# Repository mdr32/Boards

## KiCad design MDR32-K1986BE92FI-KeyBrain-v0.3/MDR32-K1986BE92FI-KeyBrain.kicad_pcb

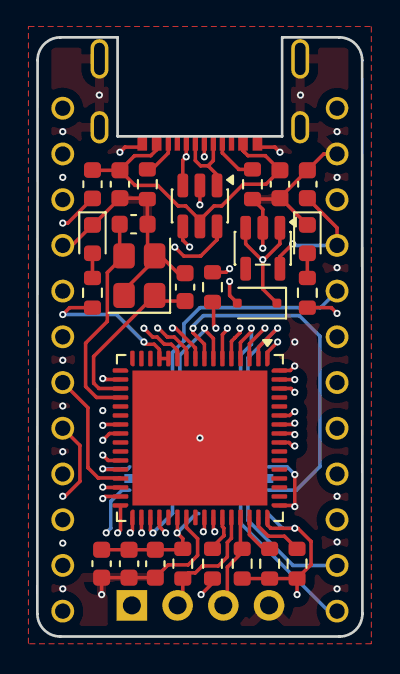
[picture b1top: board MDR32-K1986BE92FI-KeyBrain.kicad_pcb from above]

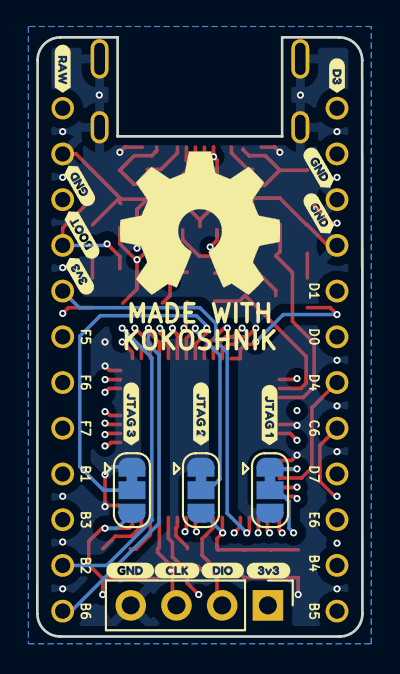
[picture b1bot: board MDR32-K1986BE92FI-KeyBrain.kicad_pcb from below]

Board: 4 copper layers, 18.1 x 33.3 mm, 46 parts (18 on the bottom side), 44 nets.

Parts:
C1: 1μF; C_0603_1608Metric
C2, C5: 10pF; C_0603_1608Metric
C3: 10μF; C_0603_1608Metric
C4, C6, C7, C8: 0.1μF; C_0603_1608Metric
D1: 3A/10V/280mV; D_SOD-323F
D2: RED; LED_0603_1608Metric
D3: GREEN; LED_0603_1608Metric
F1: 6V 0.5A MF-FSMF050X-2; Fuse_0603_1608Metric
J1: USB-C USB 2.0 MC-372; USB-C_C168688
J2: SWD; PinHeader_1x04_P2.54mm_Vertical
JP1: MODE0; SolderJumper-3_P1.3mm_Bridged12_RoundedPad1.0x1.5mm
JP2: MODE1; SolderJumper-3_P1.3mm_Bridged12_RoundedPad1.0x1.5mm
JP3: MODE2; SolderJumper-3_P1.3mm_Bridged12_RoundedPad1.0x1.5mm
R1, R2, R3, R4, R5, R6: 10K; R_0603_1608Metric
R7, R8: 5.1K; R_0603_1608Metric
R9, R10: 1K; R_0603_1608Metric
U1: AP2112K-3.3; SOT-23-5
U2: USBLC6-2SC6; SOT-23-6
U3: K1986BE92FI; QFN-64-1EP_9x9mm_P0.5mm_EP7.5x7.5mm
U4: ProMicro; pro_micro
Y1: 8MHz; Crystal_SMD_3225-4Pin_3.2x2.5mm
kibuzzard-6AC7C5DE: G***; kibuzzard-6AC7C5DE
kibuzzard-6AC7C68D, kibuzzard-6AC7C68D#2, kibuzzard-6AC7C68D#3: G***; kibuzzard-6AC7C68D
kibuzzard-6AC7C647: G***; kibuzzard-6AC7C647
kibuzzard-6ACB3A3D: G***; kibuzzard-6ACB3A3D
kibuzzard-6ACB3A18: G***; kibuzzard-6ACB3A18
kibuzzard-6ACB38A4: G***; kibuzzard-6ACB38A4
kibuzzard-6ACB38AF: G***; kibuzzard-6ACB38AF
kibuzzard-6ACB39CC: G***; kibuzzard-6ACB39CC
kibuzzard-6ACB39EC: G***; kibuzzard-6ACB39EC
kibuzzard-6ACB396A: G***; kibuzzard-6ACB396A
kibuzzard-6ACB398C: G***; kibuzzard-6ACB398C
kibuzzard-6ACB3944: G***; kibuzzard-6ACB3944

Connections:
+3.3V: C3.1, C6.1, C7.1, C8.1, J2.1, JP1.1 (A), JP2.3 (B), JP3.3 (B), R1.2, R2.2, R3.2, R4.2, R5.2, R6.2, R9.2, U1.5 (VOUT), U3.1 (UCC), U3.12 (UCC), U3.13 (BUCC), U3.24 (AUCC1), U3.28 (AUCC), U3.38 (UCC), U3.48 (UCC), U4.4 (VCC)
+5V: D1.1 (K), U1.1 (VIN), U1.3 (EN), U4.1 (RAW)
/0/TX0: U3.56 (PA7), U4.13 (PD3)
/1/RX0: U3.57 (PA6), U4.14 (PD2)
/2/SDA: U3.41 (PC1), U4.17 (PD1)
/3/SCL: U3.42 (PC0), U4.18 (PD0)
/4: U3.29 (PD7), U4.19 (PD4)
/5: U3.58 (PA5), U4.20 (PC6)
/6: U3.36 (PD6), U4.21 (PD7)
/7: U3.63 (PA0), U4.22 (PE6)
/8/TX1: U3.32 (PD1), U4.23 (PB4)
/9/RX1: U3.31 (PD0), U4.24 (PB5)
/20/SPI_CIPO: U3.5 (PF3), U4.10 (PB3)
/21/SPI_~CS: U3.4 (PF2), U4.12 (PB6)
/22/SPI_SCK: U3.3 (PF1), U4.9 (PB1)
/23/SPI_COPI: U3.2 (PF0), U4.11 (PB2)
/A0: U3.33 (PD2), U4.8 (PF7)
/A1: U3.34 (PD3), U4.7 (PF6)
/A2: U3.30 (PD4), U4.6 (PF5)
/A3: U3.35 (PD5), U4.5 (PF4)
/CLK: J2.3, R2.1, U3.45 (PB2)
/D+: J1.A6 (D+), J1.B6 (D+), U2.3 (I/O2)
/D-: J1.A7 (D-), J1.B7 (D-), U2.1 (I/O1)
/DATA+: U2.4 (I/O2), U3.9 (DP)
/DATA-: U2.6 (I/O1), U3.10 (DN)
/DIO: J2.2, R1.1, U3.44 (PB1)
/JATDI: R4.1, U3.46 (PB3)
/JATDO: R5.1, U3.43 (PB0)
/JAnTRS: R3.1, U3.47 (PB4)
/JTAG_MODE1: JP1.2 (C), U3.6 (PF4)
/JTAG_MODE2: JP2.2 (C), U3.7 (PF5)
/JTAG_MODE3: JP3.2 (C), U3.8 (PF6)
/OSC_IN: C2.1, U3.19 (OSC_IN), Y1.1
/OSC_OUT: C5.1, U3.20 (OSC_OUT), Y1.3
/USRBTN: U3.62 (PA1), U4.3 (RST)
/USRLED: R10.2, U3.59 (PA4)
/nRESET: R6.1, U3.18 (~RESET)
GND: C1.2, C2.2, C3.2, C4.2, C5.2, C6.2, C7.2, C8.2, D2.1 (K), D3.1 (K), J1.A1 (GND), J1.S1, J2.4, JP1.3 (B), JP2.1 (A), JP3.1 (A), R7.2, R8.2, U1.2 (GND), U2.2 (GND), U3.11 (GND), U3.23 (AGND1), U3.27 (AGND), U3.39 (GND), U3.49 (GND), U3.64 (GND), U3.65 (PAD), U4.2 (GND), U4.15 (GND), U4.16 (GND), Y1.2 (G), Y1.4 (G)
unnamed: D1.2 (A), F1.2
unnamed: D2.2 (A), R9.1
unnamed: D3.2 (A), R10.1
unnamed: J1.A5 (CC1), R8.1
unnamed: J1.B5 (CC2), R7.1
VBUS: C1.1, C4.1, F1.1, J1.A4 (VBUS), U2.5 (VBUS)

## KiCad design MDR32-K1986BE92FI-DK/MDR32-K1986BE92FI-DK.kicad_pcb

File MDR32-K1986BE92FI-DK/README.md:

# MDR32-K1986BE92FI-DK (Doublemint) - Отладочная плата

Отладочная плата на микроконтроллере [K1986BE92FI](https://ic.milandr.ru/products/mikrokontrollery_i_protsessory/32_razryadnye_mikrokontrollery/k1986ve92fi) от компании [Milandr](https://milandr.ru/)

## Пользовательские элементы управления:

* `RST` - кнопка для сброса питания, осуществляет полное обесточивание всей цепи питания микроконтроллера, в т.ч. даже если питание платы осуществлено через `SWD`-коннектор программатора;
* `LED GREEN` - светодиод, сигнализирующий о наличии питания платы, *не имеет обозначения на плате*;
* `USR` - пользовательская кнопка, подключена к пину `PD5`;
* `LED BLUE` - пользовательский светодиод, подключен к пину `PC2`, *не имеет обозначения на плате*;

## Особенности

Плата выполнена только для внутренних целей, тестирования возможностей микроконтроллера и разработки модулей, т.е. широкопрофильна.

По вышеуказанным целя, плата имеет свои **особенности**:

* смотри на конденсаторы на второй стороне платы, размещаются максимально близко к пинам;

* присутствуют самовосстанавливаюшщиеся предохранители на линиях `D+` и `D-` данных `USB`;

* питание платы осуществляется от USB Type-C `5V DC` или от SWD-пинов `3.3V DC`;

* на плате предусмотрен линейный понижающий регулятор до `1А`, на случай если необходимо осуществить питание переферии от самой платы;

* перемычки пинов `PE6` и `PE7`, при замыкании которых будут использоваться именно эти пины вместо часового кварцевого резонатора на `32.768KHz` (соответственно, сам резонатор и его конденсаторы должны отсутствовать на плате);

* присутствует возможность пдключения батареи (при работе батареи необходимо перевести переключатель `BT > ON`. **Важно!** Переключение выполнить согласно шелкографии, а не обозначения на групповом переключателе);

* на штыревую гребенку выведены опциональные пины `MODE[0..1]` (пины `PF4-6`) режимов работы микроконтроллера, чтобы можно было ими манипулировать для целей разработки;

Также, плата имеет свои ограничения:
* разводка платы не расчитана на высокоскоростную работу с USB;
* нет разделения по аналоговому и общему питанию, поэтому работа с аналоговым сигналом не гарантирует правильную работу$
* `USB Type-C` используется только как `USB2.0`, настоен только на `5V DC`.

---

## Демо платы:

Видеообзор платы от известного в узких кругах российского видеоблогера, смотрите на [YouTube](https://www.youtube.com/watch?v=NqpC7BkRngA) или [Rutube](https://rutube.ru/video/9d385670fd4b314179d501ec34238957/?r=wd).

> [Смотреть схему в PDF-формате](./sch_MDR32-K1986BE92FI-DK.pdf)

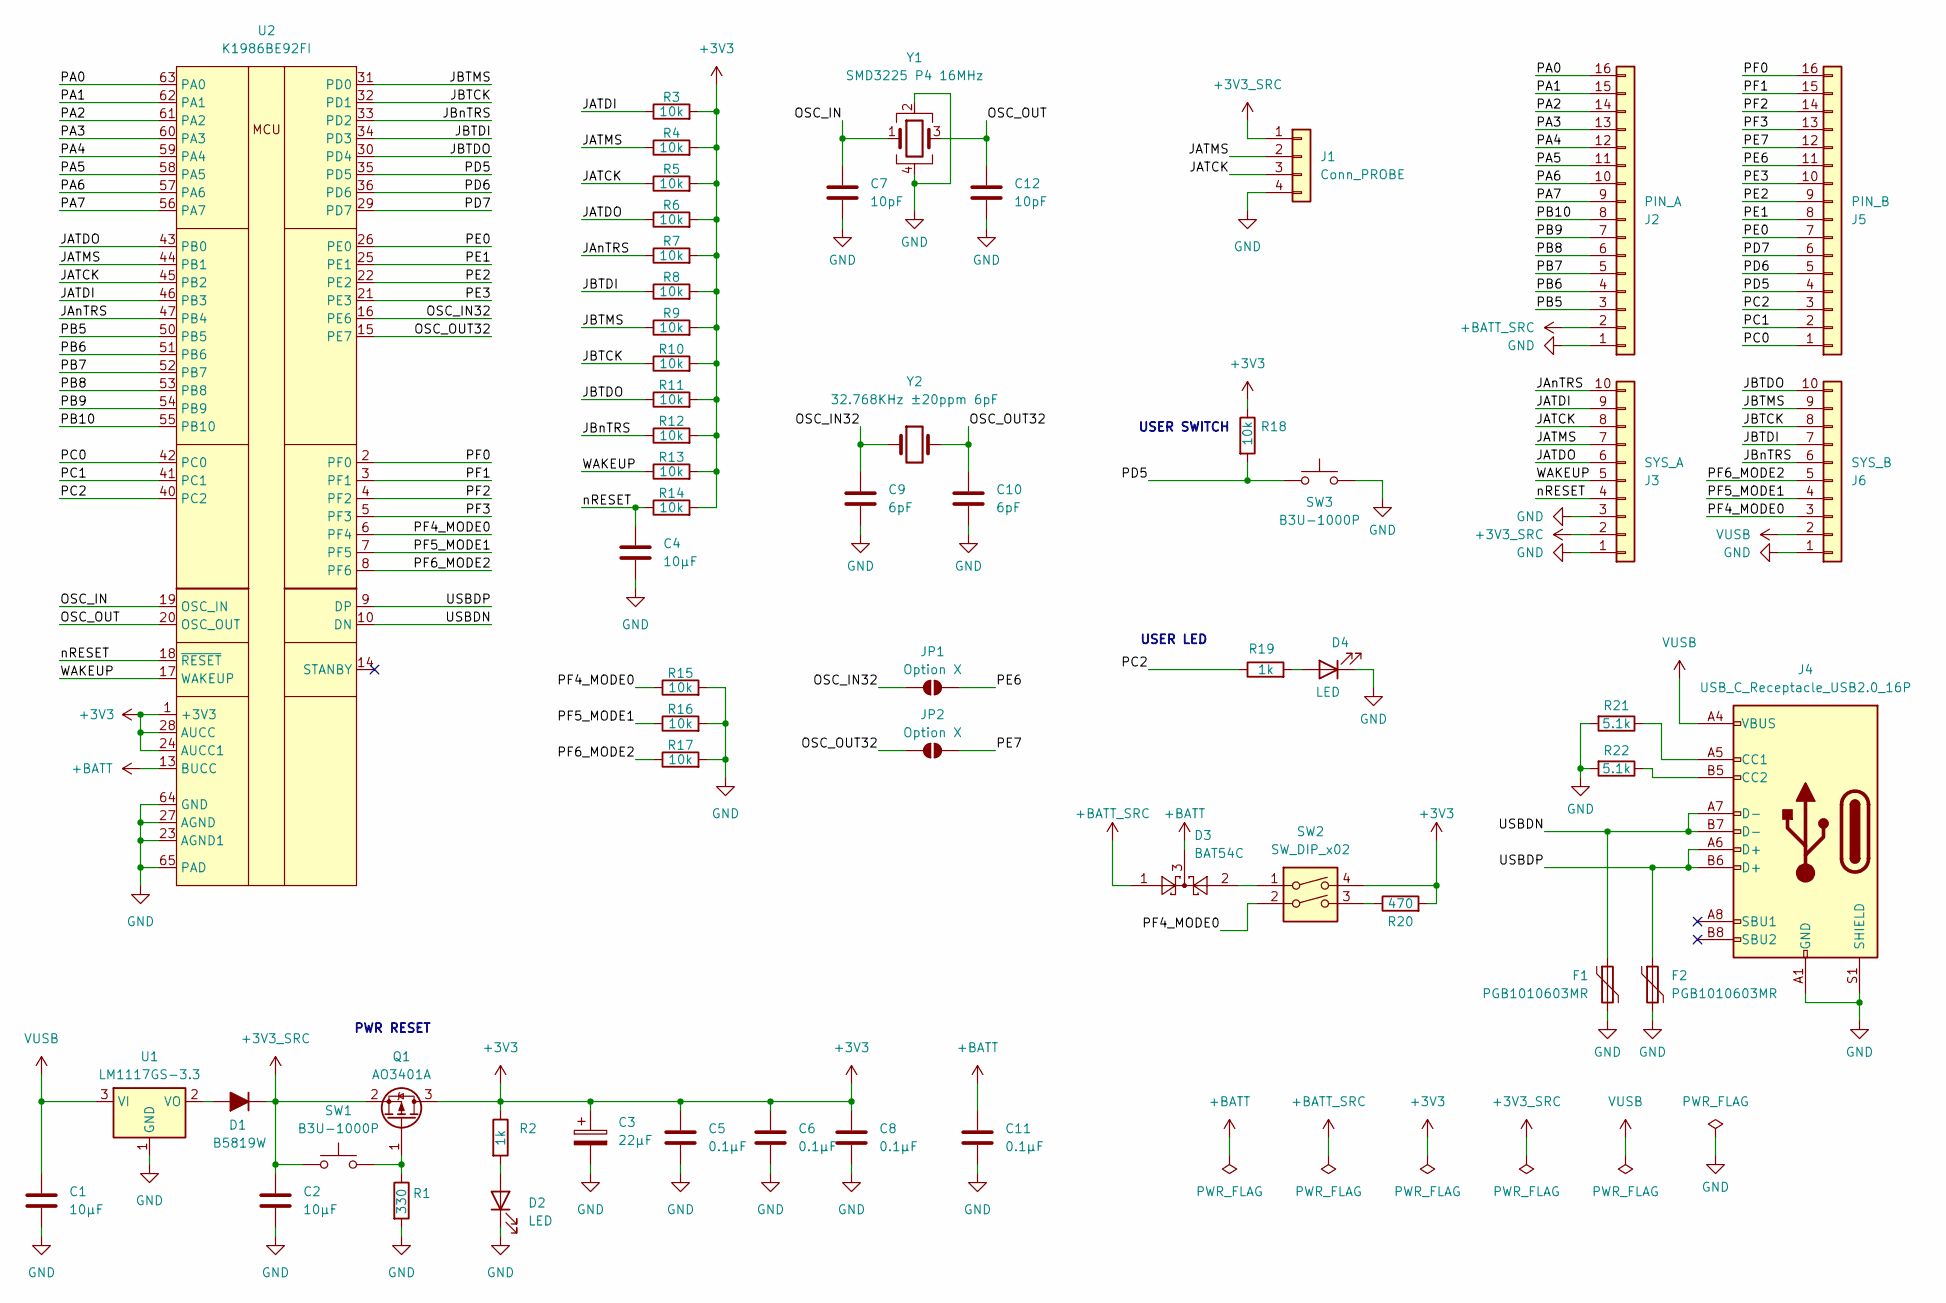
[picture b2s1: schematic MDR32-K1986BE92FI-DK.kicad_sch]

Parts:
C1, C2: 10µF; C_0805_2012Metric
C3: 22µF; CP_EIA-3216-18_Kemet-A
C4: 10µF; C_0603_1608Metric
C5, C6, C8, C11: 0.1µF; C_0603_1608Metric
C7, C12: 10pF; C_0603_1608Metric
C9, C10: 6pF; C_0603_1608Metric
D1: B5819W; D_SOD-123
D2, D4: LED; LED_0805_2012Metric
D3: BAT54C; SOT-23
F1, F2: PGB1010603MR; Fuse_0603_1608Metric
J1: Conn_PROBE; PinHeader_1x04_P2.54mm_Horizontal
J2: PIN_A; PinHeader_1x16_P2.54mm_Vertical
J3: SYS_A; PinHeader_1x10_P2.54mm_Vertical
J4: USB_C_Receptacle_USB2.0_16P; USB_C_Receptacle_GCT_USB4105-xx-A_16P_TopMnt_Horizontal
J5: PIN_B; PinHeader_1x16_P2.54mm_Vertical
J6: SYS_B; PinHeader_1x10_P2.54mm_Vertical
JP1, JP2: Option X; SolderJumper-2_P1.3mm_Open_TrianglePad1.0x1.5mm
Q1: AO3401A; SOT-23
R1: 330; R_0603_1608Metric
R2, R19: 1k; R_0603_1608Metric
R3, R4, R5, R6, R7, R8, R9, R10, R11, R12, R13, R14, R15, R16, R17, R18: 10k; R_0603_1608Metric
R20: 470; R_0603_1608Metric
R21, R22: 5.1k; R_0603_1608Metric
SW1, SW3: B3U-1000P; SW_SPST_B3U-1000P
SW2: SW_DIP_x02; SW_DIP_SPSTx02_Slide_Omron_A6H-2101_W6.15mm_P1.27mm
U1: LM1117GS-3.3; SOT-223
U2: K1986BE92FI; QFN-64-1EP_9x9mm_P0.5mm_EP7.5x7.5mm
Y1: SMD3225 P4 16MHz; Crystal_SMD_3225-4Pin_3.2x2.5mm
Y2: 32.768KHz ±20ppm 6pF; Crystal_SMD_3215-2Pin_3.2x1.5mm

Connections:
+3V3: C3.1, C5.1, C6.1, C8.1, Q1.3 (D), R2.1, R3.2, R4.2, R5.2, R6.2, R7.2, R8.2, R9.2, R10.2, R11.2, R12.2, R13.2, R14.2, R18.1, R20.2, SW2.4, U2.1 (+3V3), U2.24 (AUCC1), U2.28 (AUCC)
+3V3_SRC: C2.1, D1.1 (K), J1.1, J3.2, Q1.2 (S), SW1.1
+BATT: C11.1, D3.3, U2.13 (BUCC)
+BATT_SRC: D3.1, J2.2
/JATCK: J1.3, J3.8, R5.1, U2.45 (PB2)
/JATDI: J3.9, R3.1, U2.46 (PB3)
/JATDO: J3.6, R6.1, U2.43 (PB0)
/JATMS: J1.2, J3.7, R4.1, U2.44 (PB1)
/JAnTRS: J3.10, R7.1, U2.47 (PB4)
/JBTCK: J6.8, R10.1, U2.32 (PD1)
/JBTDI: J6.7, R8.1, U2.34 (PD3)
/JBTDO: J6.10, R11.1, U2.30 (PD4)
/JBTMS: J6.9, R9.1, U2.31 (PD0)
/JBnTRS: J6.6, R12.1, U2.33 (PD2)
/OSC_IN: C7.1, U2.19 (OSC_IN), Y1.1
/OSC_IN32: C9.1, JP1.1 (A), U2.16 (PE6), Y2.1
/OSC_OUT: C12.1, U2.20 (OSC_OUT), Y1.3
/OSC_OUT32: C10.1, JP2.1 (A), U2.15 (PE7), Y2.2
/PA0: J2.16, U2.63 (PA0)
/PA1: J2.15, U2.62 (PA1)
/PA2: J2.14, U2.61 (PA2)
/PA3: J2.13, U2.60 (PA3)
/PA4: J2.12, U2.59 (PA4)
/PA5: J2.11, U2.58 (PA5)
/PA6: J2.10, U2.57 (PA6)
/PA7: J2.9, U2.56 (PA7)
/PB5: J2.3, U2.50 (PB5)
/PB6: J2.4, U2.51 (PB6)
/PB7: J2.5, U2.52 (PB7)
/PB8: J2.6, U2.53 (PB8)
/PB9: J2.7, U2.54 (PB9)
/PB10: J2.8, U2.55 (PB10)
/PC0: J5.1, U2.42 (PC0)
/PC1: J5.2, U2.41 (PC1)
/PC2: J5.3, R19.1, U2.40 (PC2)
/PD5: J5.4, R18.2, SW3.1, U2.35 (PD5)
/PD6: J5.5, U2.36 (PD6)
/PD7: J5.6, U2.29 (PD7)
/PE0: J5.7, U2.26 (PE0)
/PE1: J5.8, U2.25 (PE1)
/PE2: J5.9, U2.22 (PE2)
/PE3: J5.10, U2.21 (PE3)
/PE6: J5.11, JP1.2 (B)
/PE7: J5.12, JP2.2 (B)
/PF0: J5.16, U2.2 (PF0)
/PF1: J5.15, U2.3 (PF1)
/PF2: J5.14, U2.4 (PF2)
/PF3: J5.13, U2.5 (PF3)
/PF4_MODE0: J6.3, R15.1, SW2.2, U2.6 (PF4)
/PF5_MODE1: J6.4, R16.1, U2.7 (PF5)
/PF6_MODE2: J6.5, R17.1, U2.8 (PF6)
/USBDN: F1.1, J4.A7 (D-), J4.B7 (D-), U2.10 (DN)
/USBDP: F2.1, J4.A6 (D+), J4.B6 (D+), U2.9 (DP)
/WAKEUP: J3.5, R13.1, U2.17 (WAKEUP)
/nRESET: C4.1, J3.4, R14.1, U2.18 (~RESET)
GND: C1.2, C2.2, C3.2, C4.2, C5.2, C6.2, C7.2, C8.2, C9.2, C10.2, C11.2, C12.2, D2.1 (K), D4.1 (K), F1.2, F2.2, J1.4, J2.1, J3.1, J3.3, J4.A1 (GND), J4.A12 (GND), J4.B1 (GND), J4.B12 (GND), J4.S1 (SHIELD), J6.1, R1.2, R15.2, R16.2, R17.2, R21.2, R22.2, SW3.2, U1.1 (GND), U2.11 (GND), U2.23 (AGND1), U2.27 (AGND), U2.39 (GND), U2.49 (GND), U2.64 (GND), U2.65 (PAD), Y1.2, Y1.4
unnamed: D1.2 (A), U1.2 (VO)
unnamed: D2.2 (A), R2.2
unnamed: D3.2, SW2.1
unnamed: D4.2 (A), R19.2
unnamed: J4.A5 (CC1), R21.1
unnamed: J4.B5 (CC2), R22.1
unnamed: Q1.1 (G), R1.1, SW1.2
unnamed: R20.1, SW2.3
VUSB: C1.1, J4.A4 (VBUS), J4.A9 (VBUS), J4.B4 (VBUS), J4.B9 (VBUS), J6.2, U1.3 (VI)

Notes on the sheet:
USER LED
PWR RESET
USER SWITCH

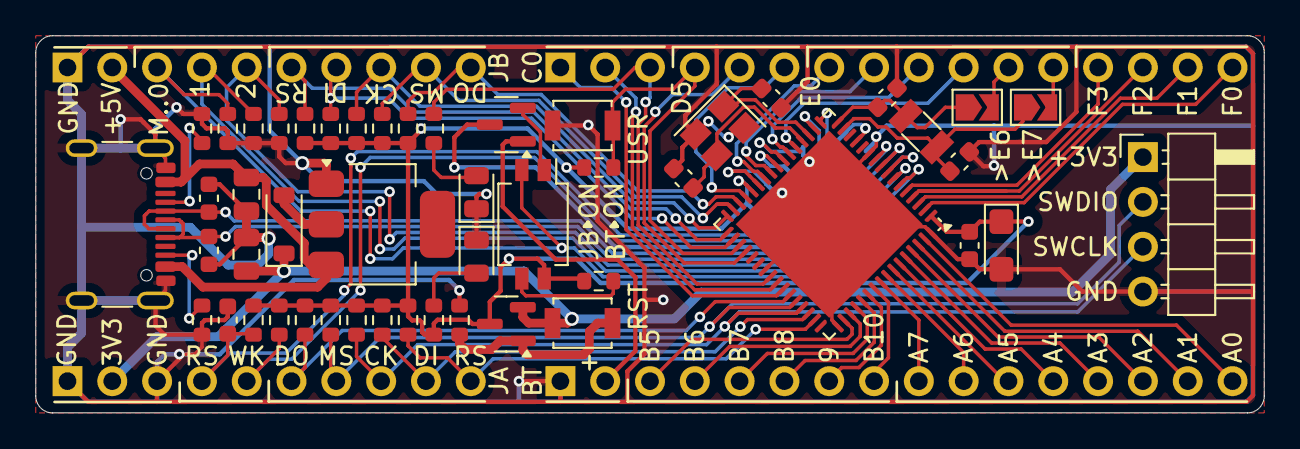
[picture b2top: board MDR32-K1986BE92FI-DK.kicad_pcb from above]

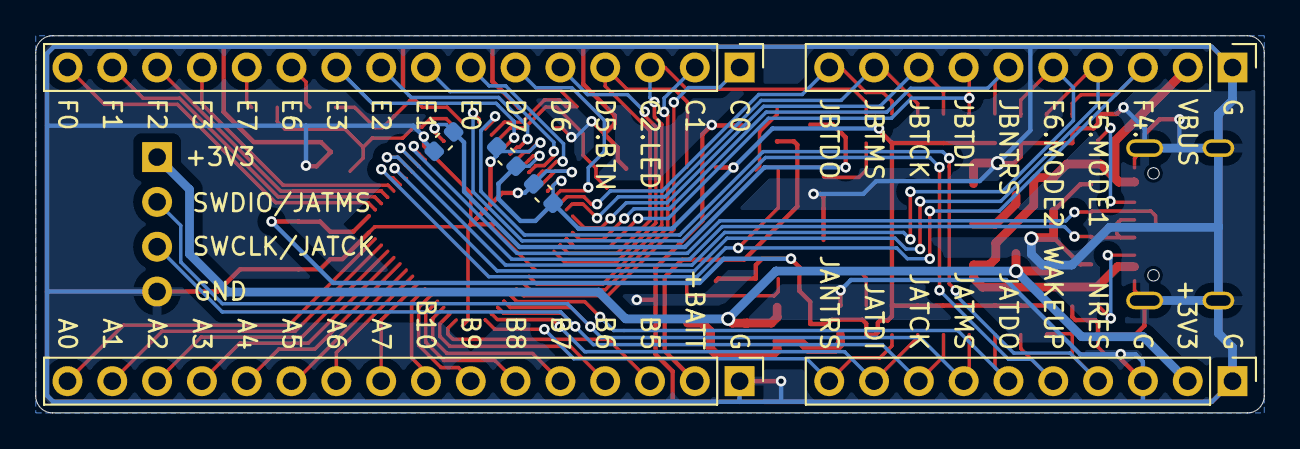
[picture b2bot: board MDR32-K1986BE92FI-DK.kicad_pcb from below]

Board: 2 copper layers, 69.6 x 21.4 mm, 56 parts (7 on the bottom side), 65 nets.

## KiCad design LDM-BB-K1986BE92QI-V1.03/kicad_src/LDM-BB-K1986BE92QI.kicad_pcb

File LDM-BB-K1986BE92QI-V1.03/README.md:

# [LDM-BB-K1986BE92QI](https://ldm-systems.ru/product/19025) - Отладочная плата

Отладочная плата на микроконтроллере [K1986BE92QI](https://ic.milandr.ru/products/mikrokontrollery_i_protsessory/32_razryadnye_mikrokontrollery/k1986ve92qi) от компании [Milandr](https://milandr.ru/)

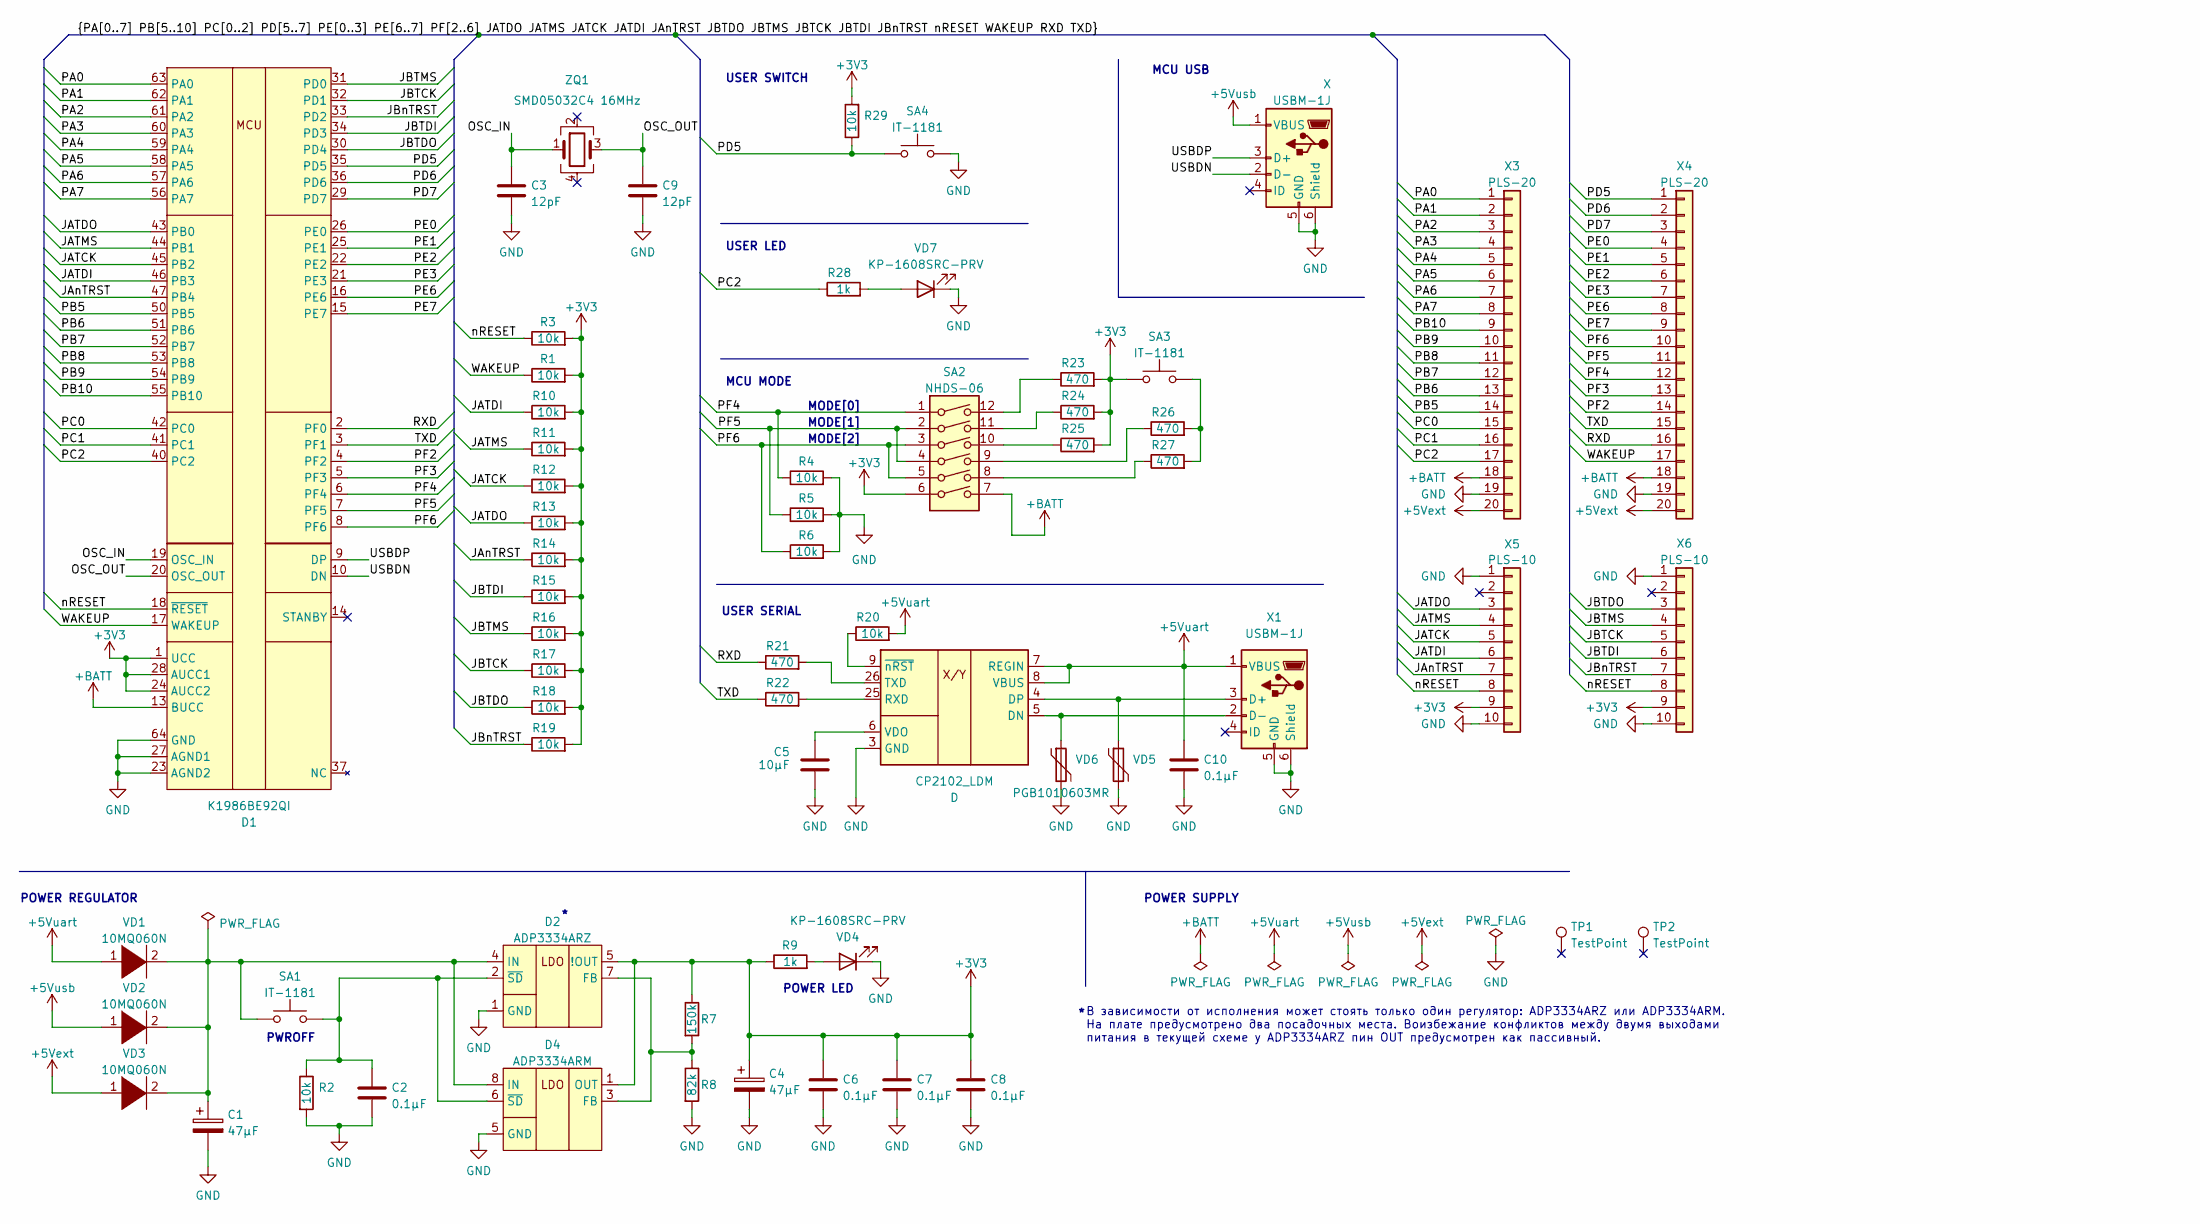
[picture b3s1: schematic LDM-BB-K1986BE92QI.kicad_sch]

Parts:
C1, C4: 47µF; CP_EIA-3528-21_Kemet-B
C2, C6, C7, C8, C10: 0.1µF; C_0603_1608Metric
C3, C9: 12pF; C_0603_1608Metric
C5: 10µF; C_1206_3216Metric
D: CP2102_LDM; QFN-28-1EP_5x5mm_P0.5mm_EP3.35x3.35mm
D1: K1986BE92QI; LQFP-64_10x10mm_P0.5mm
D2: ADP3334ARZ; SOIC-8_3.9x4.9mm_P1.27mm
D4: ADP3334ARM; MSOP-8_3x3mm_P0.65mm
R1, R2, R3, R4, R5, R6, R10, R11, R12, R13, R14, R15, R16, R17, R18, R19, R20, R29: 10k; R_0603_1608Metric
R7: 150k; R_0805_2012Metric
R8: 82k; R_0805_2012Metric
R9, R28: 1k; R_0603_1608Metric
R21, R22, R23, R24, R25, R26, R27: 470; R_0603_1608Metric
SA1, SA3, SA4: IT-1181; SW_SPST_CK_RS282G05A3
SA2: NHDS-06; SW_DIP_SPSTx06_Slide_Omron_A6H-6101_W6.15mm_P1.27mm
TP1, TP2: TestPoint; TestPoint_Pad_D1.0mm
VD1, VD2, VD3: 10MQ060N; DO-214AC
VD4, VD7: KP-1608SRC-PRV; LED_0603_1608Metric
VD5, VD6: PGB1010603MR; Fuse_0603_1608Metric
X, X1: USBM-1J; USB_Mini-B_Lumberg_2486_01_Horizontal
X3, X4: PLS-20; PinHeader_1x20_P2.54mm_Vertical
X5, X6: PLS-10; PinHeader_1x10_P2.54mm_Vertical
ZQ1: SMD05032C4 16MHz; Crystal_SMD_5032-4Pin_5.0x3.2mm

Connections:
+3V3: C4.1, C6.1, C7.1, C8.1, D1.1 (UCC), D1.12 (UCC), D1.24 (AUCC2), D1.28 (AUCC1), D1.38 (UCC), D1.48 (UCC), D2.5 (!OUT), D2.6 (!OUT), D4.1 (OUT), D4.2 (OUT), R1.2, R3.2, R7.1, R9.1, R10.2, R11.2, R12.2, R13.2, R14.2, R15.2, R16.2, R17.2, R18.2, R19.2, R23.2, R24.2, R25.2, R29.2, SA2.6, SA3.1, X5.9, X6.9
+5Vext: VD3.1 (K), X3.20, X4.20
+5Vuart: C10.1, D.7 (REGIN), D.8 (VBUS), R20.2, VD1.1 (K), X1.1 (VBUS)
+5Vusb: VD2.1 (K), X.1 (VBUS)
+BATT: D1.13 (BUCC), SA2.7, X3.18, X4.18
/JATCK: D1.45 (PB2), R12.1, X5.5
/JATDI: D1.46 (PB3), R10.1, X5.6
/JATDO: D1.43 (PB0), R13.1, X5.3
/JATMS: D1.44 (PB1), R11.1, X5.4
/JAnTRST: D1.47 (PB4), R14.1, X5.7
/JBTCK: D1.32 (PD1), R17.1, X6.5
/JBTDI: D1.34 (PD3), R15.1, X6.6
/JBTDO: D1.30 (PD4), R18.1, X6.3
/JBTMS: D1.31 (PD0), R16.1, X6.4
/JBnTRST: D1.33 (PD2), R19.1, X6.7
/OSC_IN: C3.1, D1.19 (OSC_IN), ZQ1.1
/OSC_OUT: C9.1, D1.20 (OSC_OUT), ZQ1.3
/PA0: D1.63 (PA0), X3.1
/PA1: D1.62 (PA1), X3.2
/PA2: D1.61 (PA2), X3.3
/PA3: D1.60 (PA3), X3.4
/PA4: D1.59 (PA4), X3.5
/PA5: D1.58 (PA5), X3.6
/PA6: D1.57 (PA6), X3.7
/PA7: D1.56 (PA7), X3.8
/PB5: D1.50 (PB5), X3.14
/PB6: D1.51 (PB6), X3.13
/PB7: D1.52 (PB7), X3.12
/PB8: D1.53 (PB8), X3.11
/PB9: D1.54 (PB9), X3.10
/PB10: D1.55 (PB10), X3.9
/PC0: D1.42 (PC0), X3.15
/PC1: D1.41 (PC1), X3.16
/PC2: D1.40 (PC2), R28.1, X3.17
/PD5: D1.35 (PD5), R29.1, SA4.1, X4.1
/PD6: D1.36 (PD6), X4.2
/PD7: D1.29 (PD7), X4.3
/PE0: D1.26 (PE0), X4.4
/PE1: D1.25 (PE1), X4.5
/PE2: D1.22 (PE2), X4.6
/PE3: D1.21 (PE3), X4.7
/PE6: D1.16 (PE6), X4.8
/PE7: D1.15 (PE7), X4.9
/PF2: D1.4 (PF2), X4.14
/PF3: D1.5 (PF3), X4.13
/PF4: D1.6 (PF4), R4.1, SA2.1, X4.12
/PF5: D1.7 (PF5), R5.1, SA2.2, SA2.4, X4.11
/PF6: D1.8 (PF6), R6.1, SA2.3, SA2.5, X4.10
/RXD: D1.2 (PF0), R21.1, X4.16
/TXD: D1.3 (PF1), R22.1, X4.15
/USBDN: D1.10 (DN), X.2 (D-)
/USBDP: D1.9 (DP), X.3 (D+)
/WAKEUP: D1.17 (WAKEUP), R1.1, X4.17
/nRESET: D1.18 (~RESET), R3.1, X5.8, X6.8
GND: C1.2, C2.2, C3.2, C4.2, C5.1, C6.2, C7.2, C8.2, C9.2, C10.2, D.3 (GND), D.29 (PAD), D1.11 (GND), D1.23 (AGND2), D1.27 (AGND1), D1.39 (GND), D1.49 (GND), D1.64 (GND), D2.1 (GND), D4.5 (GND), R2.2, R4.2, R5.2, R6.2, R8.2, SA4.2, VD4.1 (K), VD5.2, VD6.2, VD7.1 (K), X.5 (GND), X.6 (Shield), X1.5 (GND), X1.6 (Shield), X3.19, X4.19, X5.1, X5.10, X6.1, X6.10
IN: C1.1, D2.3 (IN), D2.4 (IN), D4.7 (IN), D4.8 (IN), SA1.1, VD1.2 (A), VD2.2 (A), VD3.2 (A)
unnamed: C2.1, D2.2 (~SD), D4.6 (~SD), R2.1, SA1.2
unnamed: C5.2, D.6 (VDO)
unnamed: D2.7 (FB), D4.3 (FB), R7.2, R8.1
unnamed: R9.2, VD4.2 (A)
unnamed: D.9 (~nRST), R20.1
unnamed: D.26 (TXD), R21.2
unnamed: D.25 (RXD), R22.2
unnamed: R23.1, SA2.12
unnamed: R24.1, SA2.11
unnamed: R25.1, SA2.10
unnamed: R26.1, SA2.9
unnamed: R26.2, R27.2, SA3.2
unnamed: R27.1, SA2.8
unnamed: R28.2, VD7.2 (A)
unnamed: D.4 (DP), VD5.1, X1.3 (D+)
unnamed: D.5 (DN), VD6.1, X1.2 (D-)

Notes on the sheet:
POWER REGULATOR
MODE[0]
MCU MODE
MODE[2]
POWER LED
USER LED
MODE[1]
USER SWITCH
POWER SUPPLY
MCU USB
В зависимости от исполнения может стоять только один регулятор: ADP3334ARZ или ADP3334ARM. На плате предусмотрено два посадочных места. Воизбежание конфликтов между двумя выходами питания в текущей схеме у ADP3334ARZ пин OUT предусмотрен как пассивный.
PWROFF
USER SERIAL

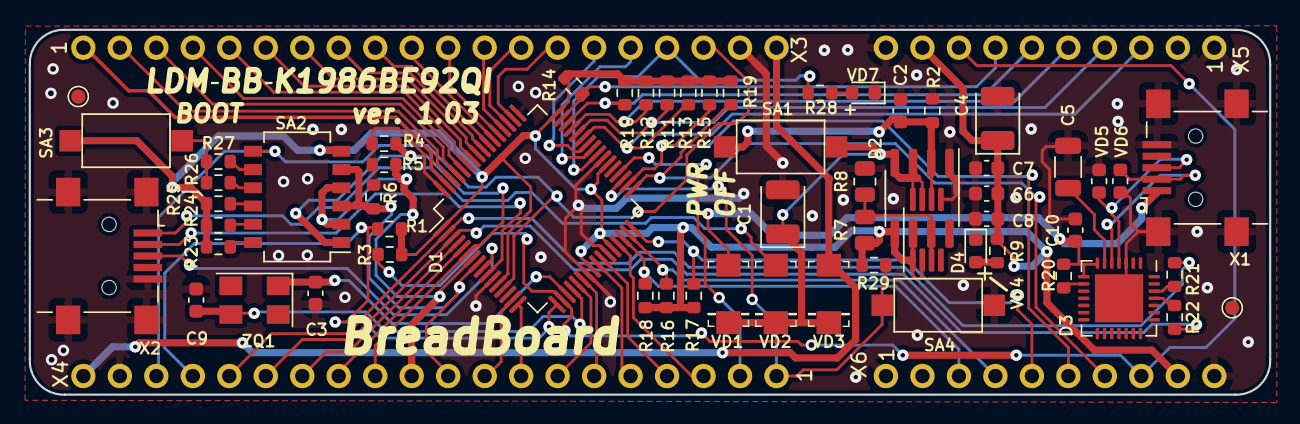
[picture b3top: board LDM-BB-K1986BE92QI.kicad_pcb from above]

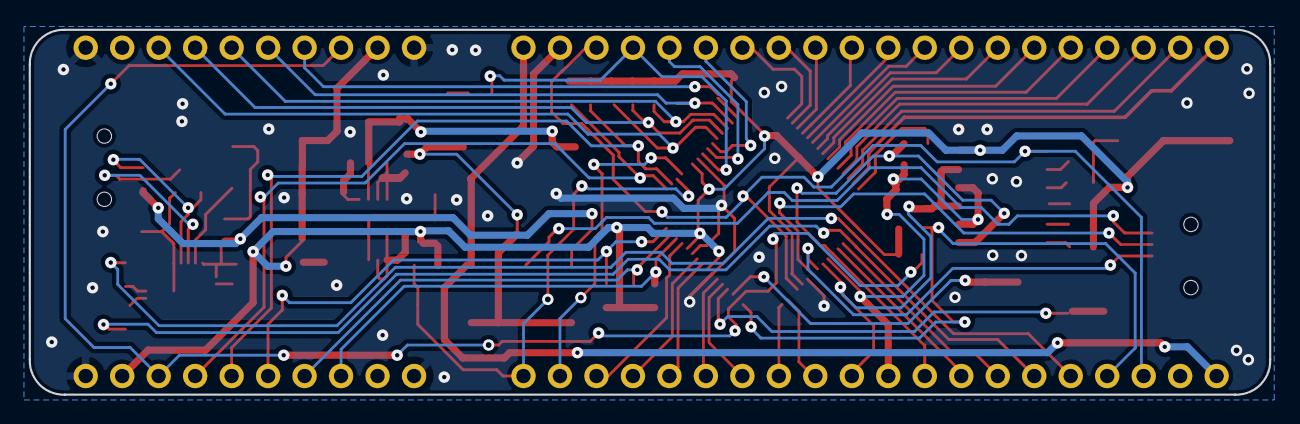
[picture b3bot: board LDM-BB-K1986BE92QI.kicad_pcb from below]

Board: 2 copper layers, 86.4 x 25.4 mm, 63 parts (4 on the bottom side), 72 nets.

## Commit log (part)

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2022-06-08 add board LDM-BB-K1986BE92QI-V1.03
2022-06-08 документация производителя и демо проект
2022-06-12 фикс игнор-листа
2022-06-13 + изображение схемы
2024-09-11 старт описания
2024-09-11 add gitignore
2024-12-05 Symbol MDR32 dev kit board
2024-12-05 add gitignore *.lck file
2024-12-05 fix probe connector
2024-12-05 symbol rename and fixed
2024-12-05 add net list
2024-12-05 net link by symbol
2024-12-05 fix batt pin names
2024-12-05 create pcb blank
2024-12-06 add route restrictions
2024-12-06 start pcb sizes
2024-12-06 change pinout on header
2024-12-07 position and sizes
2024-12-07 usb position on pcb
2024-12-07 fix position
2024-12-07 update footprints
2024-12-07 position SW pinout
2024-12-08 part made
2024-12-10 fix sw pin header
2024-12-10 exclude battery holder
2024-12-10 update cap sizes
2024-12-10 update resistors sizes
2024-12-10 update LED sizes
2024-12-10 part position
2024-12-12 start route
2024-12-12 part route
2025-01-19 unctional route and dependencies
2025-01-19 silk final
2025-01-19 final draw
2025-01-20 add exclude
2025-01-20 create manufatered files
2025-01-26 update net list
2025-01-26 fix 3d model for QFN-64
2025-01-26 temporary changes
2025-01-27 add local crystals
2025-01-27 SOT-223
2025-01-27 USB_C
2025-01-27 PinHeader_1x04
2025-01-27 SW_Push
2025-01-27 SW_DIP_x02
2025-01-27 Resistors
2025-01-27 SOT-23
2025-01-27 SolderJumper
2025-01-27 PinHeader
2025-01-27 Fuse
2025-01-27 diod
2025-01-27 Cap_Tantalum
2025-01-27 Move local for archive (#1)
    Move symbol and footprint to local for archive
2025-01-27 rename
2025-01-28 add README.md
2025-01-28 remove file on manufacture
2025-01-28 ignore file manufacture
2025-02-06 change path to kicad source directory
2025-02-06 add description and image board
2025-02-06 change title
2025-02-06 MDR32-K1986BE92FI-DK add board (#2)
2025-02-08 add to ignore
2025-03-04 удаляем и запрещаем локальные файлы
2025-09-28 Update README.md
    add link on video
2026-05-28 MDR32-K1986BE92FI-KeyBrain: gitignore файлов от новой версии kicad
2026-05-28 MDR32-K1986BE92FI-KeyBrain: добавляем стартовые файлы проекта
2026-06-02 MDR32-K1986BE92FI-KeyBrain: * выравниваем библиотеки * питание и USB в УГО
2026-06-02 update schematic for KeyBrain
2026-06-04 MDR32-K1986BE92FI-KeyBrain: более явные имена у пинов для SWD
2026-06-04 MDR32-K1986BE92FI-KeyBrain: резистивная подтяжка сервисных пинов
2026-06-04 MDR32-K1986BE92FI-KeyBrain: некоторые пины
2026-06-04 MDR32-K1986BE92FI-KeyBrain: Пробуем вариант с портам A
2026-06-06 MDR32-K1986BE92FI-KeyBrain: add diff pairs and comments on schematic
2026-06-06 MDR32-K1986BE92FI-KeyBrain: add footprints and crystal
2026-06-06 MDR32-K1986BE92FI-KeyBrain: update footprints, BOM & schematic
2026-06-08 add components to pcb
2026-06-09 MDR32-K1986BE92FI-KeyBrain: rename SWD-pins
2026-06-09 MDR32-K1986BE92FI-KeyBrain: mode select own pins
2026-06-09 MDR32-K1986BE92FI-KeyBrain: less pcb options by only WAKEUP
2026-06-09 MDR32-K1986BE92FI-KeyBrain: i2c pinout position
2026-06-09 MDR32-K1986BE92FI-KeyBrain: release unconnected
2026-06-09 MDR32-K1986BE92FI-KeyBrain: fix errors
2026-06-09 MDR32-K1986BE92FI-KeyBrain: set jumper footprints
2026-06-09 fix usb footprint
2026-06-24 MDR32-K1986BE92FI-KeyBrain: fix swd header
2026-06-24 MDR32-K1986BE92FI-KeyBrain: add usb fottprint
2026-06-24 MDR32-K1986BE92FI-KeyBrain: фикс символа кристалла
2026-06-24 MDR32-K1986BE92FI-KeyBrain: фикс символа USB
2026-06-24 MDR32-K1986BE92FI-KeyBrain: fix символа ProMicro
2026-06-24 MDR32-K1986BE92FI-KeyBrain: небольшая корректировка в позиции
2026-06-24 MDR32-K1986BE92FI-KeyBrain: создаем net-лист
2026-06-25 MDR32-K1986BE92FI-KeyBrain: загружаем net-лист и обновляем измененные элементы
2026-06-25 MDR32-K1986BE92FI-KeyBrain: микроправки
2026-06-25 MDR32-K1986BE92FI-KeyBrain: настройки ограничений для Резонита и предустановленные размеры
2026-06-25 MDR32-K1986BE92FI-KeyBrain: игнорируем lock-файлы
2026-06-25 MDR32-K1986BE92FI-KeyBrain: игнорируем снапшоты
2026-06-25 MDR32-K1986BE92FI-KeyBrain: группируем и перепозиционируем
2026-06-26 MDR32-K1986BE92FI-KeyBrain: частичное позиционирование
